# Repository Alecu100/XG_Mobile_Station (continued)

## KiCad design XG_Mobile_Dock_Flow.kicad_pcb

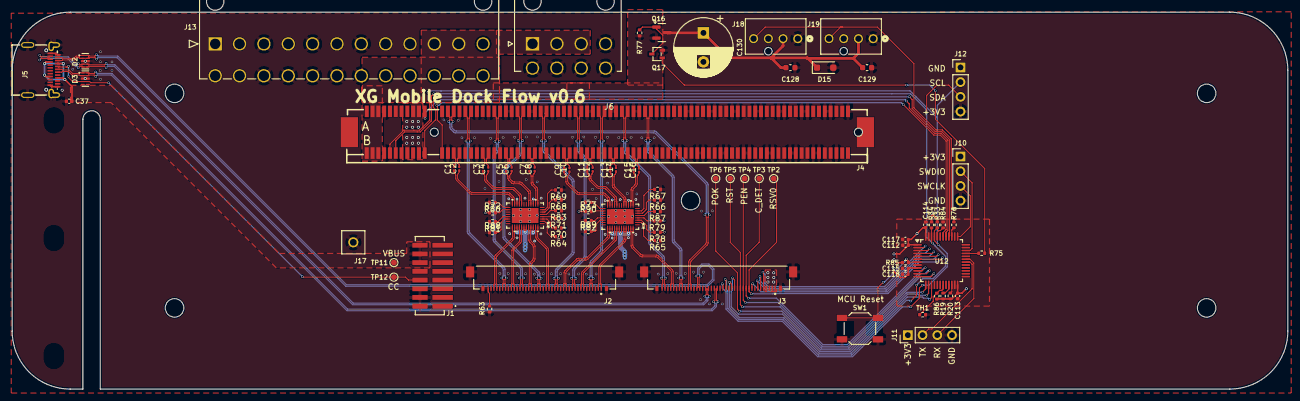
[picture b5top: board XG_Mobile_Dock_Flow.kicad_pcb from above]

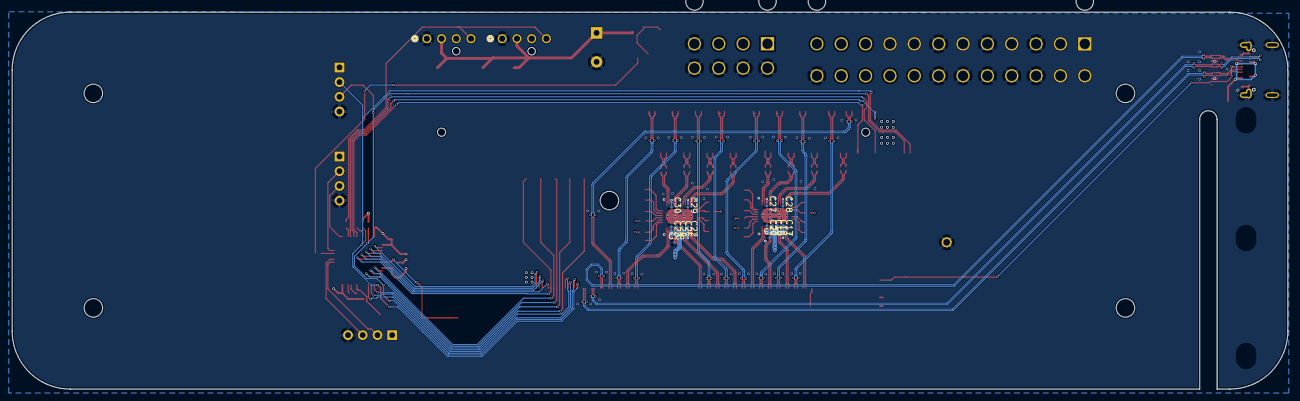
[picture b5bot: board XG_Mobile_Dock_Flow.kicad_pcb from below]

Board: 4 copper layers, 220.0 x 65.0 mm, 101 parts (14 on the bottom side), 133 nets.

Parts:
C1, C2, C3, C4, C5, C6, C7, C8, C9, C10, C11, C12, C13, C14, C15, C16: 220nF; C_0201_0603Metric
C17, C18, C19, C20, C22, C23, C24, C25, C27, C28, C29, C30: 100nF; C_0201_0603Metric
C21, C26: 1μF; C_0201_0603Metric
C37: 0.1μF; C_0402_1005Metric
C112, C113, C114: 0.1µF; C_0402_1005Metric
C115: 10nF; C_0402_1005Metric
C117: 4.7µF; C_0402_1005Metric
C118: 1µF; C_0402_1005Metric
C128, C129: 0.1µF; C_0603_1608Metric
C130: 470µF; CP_Radial_D10.0mm_P5.00mm
D2, D3: H5VU25U; AZ1045-04F
D15: 1N4007; D_SOD-123F
J1: 5-1775443-8
J2, J3: 20455-040E-76
J4: 3-2362375-4; CONN-SMD_164P-P1.00-V_3133
J5: USB_C_Receptacle; USB-C-SMD_TYPE-C-24P-QT
J6: 455860005; MOLEX_455860005
J10: SWD; PinHeader_1x04_P2.54mm_Vertical
J11: UART; PinHeader_1x04_P2.54mm_Vertical
J12: I2C1; PinHeader_1x04_P2.54mm_Vertical
J13: 39301240; CON_39300240
J17: 8730; KEYSTONE_8730
J18, J19: CONN_SD-47053-001_H10p00_MOL
Q16: AO3401A; SOT-23
Q17: 2N7002W; SOT-323-3_L2.0-W1.3-P1.30-LS2.1-BR
R19, R20, R70, R71, R72, R73, R78, R79, R80, R81, R82, R90: 4.7k; R_0402_1005Metric
R33, R34, R63, R77, R85: 10k; R_0402_1005Metric
R64, R65, R84, R88, R89: 1k; R_0402_1005Metric
R66, R67, R68, R69, R83, R87: 59k; R_0402_1005Metric
R75: 100; R_0402_1005Metric
R76: 330; R_0402_1005Metric
R86: 100k; R_0402_1005Metric
SW1: SW_Push; SW_SPST_SKQG_WithStem
TH1: NCP15WF104F03RC; R_0402_1005Metric
TP2, TP3, TP4, TP5, TP6, TP11, TP12: TestPoint_Small; TestPoint_Pad_D1.0mm
U1, U2: DS160PR410RNQR; WQFN_RNQ40_TEX
U12: STM32F030C8Tx; LQFP-48_7x7mm_P0.5mm

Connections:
+3V3: C17.2, C18.2, C19.2, C20.2, C21.2, C22.2, C23.2, C24.2, C25.2, C26.2, C112.1, C113.1, C114.1, C115.1, C117.1, C118.1, J3.1 (+3.3V), J3.2 (+3.3V), J3.3 (+3.3V), J3.4 (+3.3V), J4.A9, J4.A10, J4.B8, J4.B10, J10.1, J11.1, J12.1, J13.1, J13.2, J13.12, J13.13, R19.1, R20.1, R33.1, R34.1, R70.1, R71.1, R72.1, R73.1, R78.1, R79.1, R85.2, R86.2, U1.31 (VDD), U1.34 (VDD), U1.35 (VDD), U1.38 (VDD), U2.31 (VDD), U2.34 (VDD), U2.35 (VDD), U2.38 (VDD), U12.1 (VDD), U12.9 (VDDA), U12.24 (VDD), U12.48 (VDD)
+12V: J4.A2, J4.A3, J4.B1, J4.B2, J4.B3, J6.1, J6.2, J6.3, J13.10, J13.11, Q16.2 (S), R77.1
/AC_LOSS: J3.15 (P_AC_LOSS), U12.14 (PA4)
/CC: D3.4 (I/O_3), D3.7 (NC), J1.13 (CC), J5.A5 (CC1), TP12.1
/CLKN: J3.30 (PCIE_CLKN), J4.A14
/CLKP: J3.31 (PCIE_CLKP), J4.A13
/CLKREQ#: J4.B12, U12.42 (PB6)
/CON_DET: J3.11 (CON_DET), TP3.1, U12.10 (PA0)
/C_DN: D3.2 (I/O_2), D3.9 (NC), J3.21 (USB_DM), J5.A7 (D-)
/C_DP: D3.1 (I/O_1), D3.10 (NC), J3.22 (USB_DP), J5.A6 (D+)
/C_RXN: D2.5 (I/O_4), D2.6 (NC), J3.24 (USB_RXN), J5.B10 (RX1-)
/C_RXP: D2.4 (I/O_3), D2.7 (NC), J3.25 (USB_RXP), J5.B11 (RX1+)
/C_TXN: D2.2 (I/O_2), D2.9 (NC), J3.28 (USB_TXP), J5.A3 (TX1-)
/C_TXP: D2.1 (I/O_1), D2.10 (NC), J3.27 (USB_TXN), J5.A2 (TX1+)
/DET: J2.40 (CON_DET_TOWER#), R63.1
/HSI0N: J2.34 (PCIE_RXN0), J4.A17
/HSI0P: J2.35 (PCIE_RXP0), J4.A16
/HSI1N: J2.28 (PCIE_RXN1), J4.A22
/HSI1P: J2.29 (PCIE_RXP1), J4.A21
/HSI2N: J2.22 (PCIE_RXN2), J4.A26
/HSI2P: J2.23 (PCIE_RXP2), J4.A25
/HSI3N: J2.16 (PCIE_RXN3), J4.A30
/HSI3P: J2.17 (PCIE_RXP3), J4.A29
/HSI4N: J2.10 (PCIE_RXN4), J4.A36
/HSI4P: J2.11 (PCIE_RXP4), J4.A35
/HSI5N: J2.4 (PCIE_RXN5), J4.A40
/HSI5P: J2.5 (PCIE_RXP5), J4.A39
/HSI6N: J3.39 (PCIE_RXN6), J4.A44
/HSI6P: J3.40 (PCIE_RXP6), J4.A43
/HSI7N: J3.33 (PCIE_RXN7), J4.A48
/HSI7P: J3.34 (PCIE_RXP7), J4.A47
/HSO0N: C2.2, J4.B15
/HSO0P: C1.2, J4.B14
/HSO1N: C4.2, J4.B20
/HSO1P: C3.2, J4.B19
/HSO2N: C6.2, J4.B24
/HSO2P: C5.2, J4.B23
/HSO3N: C8.2, J4.B28
/HSO3P: C7.2, J4.B27
/HSO4N: C10.2, J4.B34
/HSO4P: C9.2, J4.B33
/HSO5N: C12.2, J4.B38
/HSO5P: C11.2, J4.B37
/HSO6N: C14.2, J4.B42
/HSO6P: C13.2, J4.B41
/HSO7N: C16.2, J4.B46
/HSO7P: C15.2, J4.B45
/HSOL0N: J2.37 (PCIE_TXN0), U1.30 (RX0N)
/HSOL0P: J2.38 (PCIE_TXP0), U1.29 (RX0P)
/HSOL1N: J2.31 (PCIE_TXN1), U1.33 (RX1N)
/HSOL1P: J2.32 (PCIE_TXP1), U1.32 (RX1P)
/HSOL2N: J2.25 (PCIE_TXN2), U1.37 (RX2N)
/HSOL2P: J2.26 (PCIE_TXP2), U1.36 (RX2P)
/HSOL3N: J2.19 (PCIE_TXN3), U1.40 (RX3N)
/HSOL3P: J2.20 (PCIE_TXP3), U1.39 (RX3P)
/HSOL4N: J2.13 (PCIE_TXN4), U2.30 (RX0N)
/HSOL4P: J2.14 (PCIE_TXP4), U2.29 (RX0P)
/HSOL5N: J2.7 (PCIE_TXN5), U2.33 (RX1N)
/HSOL5P: J2.8 (PCIE_TXP5), U2.32 (RX1P)
/HSOL6N: J2.1 (PCIE_TXN6), U2.37 (RX2N)
/HSOL6P: J2.2 (PCIE_TXP6), U2.36 (RX2P)
/HSOL7N: J3.36 (PCIE_TXN7), U2.40 (RX3N)
/HSOL7P: J3.37 (PCIE_TXP7), U2.39 (RX3P)
/HSOT0N: C2.1, U1.19 (TX0N)
/HSOT0P: C1.1, U1.20 (TX0P)
/HSOT1N: C4.1, U1.16 (TX1N)
/HSOT1P: C3.1, U1.17 (TX1P)
/HSOT2N: C6.1, U1.12 (TX2N)
/HSOT2P: C5.1, U1.13 (TX2P)
/HSOT3N: C8.1, U1.9 (TX3N)
/HSOT3P: C7.1, U1.10 (TX3P)
/HSOT4N: C10.1, U2.19 (TX0N)
/HSOT4P: C9.1, U2.20 (TX0P)
/HSOT5N: C12.1, U2.16 (TX1N)
/HSOT5P: C11.1, U2.17 (TX1P)
/HSOT6N: C14.1, U2.12 (TX2N)
/HSOT6P: C13.1, U2.13 (TX2P)
/HSOT7N: C16.1, U2.9 (TX3N)
/HSOT7P: C15.1, U2.10 (TX3P)
/LED_RED#: J3.7 (LED_R), U12.4 (PC15)
/LED_WHITE#: J3.6 (LED_W), U12.3 (PC14)
/LOCK_DET: J3.9 (CON_SW1_DET), U12.5 (PF0)
/LOCK_SW: J3.5 (LOCK_SW), U12.2 (PC13)
/MCU/FAN_ON: R75.1, U12.33 (PA12)
/MCU/FAN_PWM: R76.1, U12.39 (PB3)
/MCU/RX: J11.3, U12.31 (PA10)
/MCU/SCL2: R19.2, U12.21 (PB10)
/MCU/SDA2: R20.2, U12.22 (PB11)
/MCU/SWCLK: J10.3, U12.37 (PA14)
/MCU/SWDIO: J10.2, U12.34 (PA13)
/MCU/TX: J11.2, U12.30 (PA9)
/MCU_IRQ#: J3.16 (MCU_IRQ#), U12.15 (PA5)
/PERST#: J4.A11, U12.41 (PB5)
/PWREN#: J3.12 (PWR_EN#), TP4.1, U12.11 (PA1)
/PWROK: J3.14 (PWROK), TP6.1, U12.13 (PA3)
/RST#: J3.13 (RST#), TP5.1, U12.12 (PA2)
/RST_SW: R85.1, SW1.1, U12.7 (NRST)
/RSV0: J3.10, TP2.1, U12.6 (PF1)
/SCL: J3.19 (SMB1_CLK), J4.B5, J12.2, R33.2, U12.45 (PB8)
/SDA: J3.18 (SMB1_DAT), J4.B6, J12.3, R34.2, U12.46 (PB9)
/VBUS: C37.1, J1.9 (VBUS), J1.10 (VBUS), J1.11 (VBUS), J5.A4 (VBUS), J5.A9 (VBUS), J5.B4 (VBUS), J5.B9 (VBUS), TP11.1
/WAKE#: J4.B11, U12.40 (PB4)
GND: C17.1, C18.1, C19.1, C20.1, C21.1, C22.1, C23.1, C24.1, C25.1, C26.1, C27.2, C28.2, C29.2, C30.2, C37.2, C112.2, C113.2, C114.2, C115.2, C117.2, C118.2, C128.2, C129.2, C130.2, D2.3 (GND), D2.8 (GND), D3.3 (GND), D3.8 (GND), D15.2 (A), J1.14 (GND), J1.15 (GND), J1.16 (GND), J2.3 (GND), J2.6 (GND), J2.9 (GND), J2.12 (GND), J2.15 (GND), J2.18 (GND), J2.21 (GND), J2.24 (GND), J2.27 (GND), J2.30 (GND), J2.33 (GND), J2.36 (GND), J2.39 (GND), J2.S1 (SHIELD), J2.S2 (SHIELD), J2.S3 (SHIELD), J2.S4 (SHIELD), J3.17 (GND), J3.20 (GND), J3.23 (GND), J3.26 (GND), J3.29 (GND), J3.32 (GND), J3.35 (GND), J3.38 (GND), J3.S1 (SHIELD), J3.S2 (SHIELD), J3.S3 (SHIELD), J3.S4 (SHIELD), J4.A4, J4.A12, J4.A15, J4.A18, J4.A20, J4.A23, J4.A24, J4.A27, J4.A28, J4.A31, J4.A34, J4.A37, J4.A38, J4.A41, J4.A42, J4.A45, J4.A46, J4.A49, J4.A51, J4.A54, J4.A55, J4.A58, J4.A59, J4.A62, J4.A63, J4.A66, J4.A67, J4.A70, J4.A71, J4.A74, J4.A75, J4.A78, J4.A79, J4.A82, J4.B4, J4.B7, J4.B13, J4.B16, J4.B18, J4.B21, J4.B22, J4.B25, J4.B26, J4.B29, J4.B32, J4.B35, J4.B36, J4.B39, J4.B40, J4.B43, J4.B44, J4.B47, J4.B49, J4.B52, J4.B53, J4.B56, J4.B57, J4.B60, J4.B61, J4.B64, J4.B65, J4.B68, J4.B69, J4.B72, J4.B73, J4.B76, J4.B77, J4.B80, J5.A1 (GND), J5.A12 (GND), J5.B1 (GND), J5.B12 (GND), J5.S1 (SHIELD), J6.4, J6.5, J6.6, J6.7, J6.8, J10.4, J11.4, J12.4, J13.3, J13.5, J13.7, J13.15, J13.16, J13.17, J13.18, J13.19, J13.24, J17.1, J18.1, J19.1, Q17.2 (S), R63.2, R64.1, R65.1, R66.1, R67.1, R68.1, R69.1, R80.2, R81.2, R82.2, R83.1, R84.1, R87.1, R88.1, R89.1, R90.2, SW1.2, TH1.2, U1.41 (GND), U2.41 (GND), U12.8 (VSSA), U12.23 (VSS), U12.47 (VSS)
unnamed: C128.1, C129.1, C130.1, D15.1 (K), J18.2, J19.2, Q16.3 (D)
unnamed: J18.4, J19.4, R76.2
unnamed: Q16.1 (G), Q17.3 (D), R77.2
unnamed: Q17.1 (G), R75.2
unnamed: R64.2, U1.2 (EN_SMB)
unnamed: R69.2, U1.7 (EQ0_ADDR0)
unnamed: R68.2, U1.6 (EQ1_ADDR1)
unnamed: R83.2, U1.5 (GAIN)
unnamed: R80.1, U1.21 (PWDN1)
unnamed: R81.1, U1.25 (PWDN2)
unnamed: R72.2, U1.22 (READ_EN_N)
unnamed: R88.2, U1.26 (RX_DET)
unnamed: R70.2, U1.3 (SCL)
unnamed: R71.2, U1.4 (SDA)
unnamed: C28.1, U1.18 (VREF)
unnamed: C27.1, U1.11 (VREG)
unnamed: R65.2, U2.2 (EN_SMB)
unnamed: R67.2, U2.7 (EQ0_ADDR0)
unnamed: R66.2, U2.6 (EQ1_ADDR1)
unnamed: R87.2, U2.5 (GAIN)
unnamed: R90.1, U2.21 (PWDN1)
unnamed: R82.1, U2.25 (PWDN2)
unnamed: R73.2, U2.22 (READ_EN_N)
unnamed: R89.2, U2.26 (RX_DET)
unnamed: R78.2, U2.3 (SCL)
unnamed: R79.2, U2.4 (SDA)
unnamed: C29.1, U2.18 (VREF)
unnamed: C30.1, U2.11 (VREG)
unnamed: R84.2, U12.44 (BOOT0)
unnamed: R86.1, TH1.1, U12.19 (PB1)

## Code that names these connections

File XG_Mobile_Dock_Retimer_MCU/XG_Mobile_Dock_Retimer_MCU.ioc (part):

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Mcu.Name=STM32F405RGTx
Mcu.Package=LQFP64
Mcu.UserName=STM32F405RGTx
PA0-WKUP.GPIOParameters=GPIO_PuPd,GPIO_Label,GPIO_ModeDefaultEXTI
PA0-WKUP.GPIO_Label=CON_DET
PA0-WKUP.GPIO_ModeDefaultEXTI=GPIO_MODE_IT_RISING_FALLING
PA0-WKUP.GPIO_PuPd=GPIO_PULLUP
PA0-WKUP.Signal=GPXTI0
PA1.GPIOParameters=GPIO_PuPd,GPIO_Label,GPIO_ModeDefaultEXTI
PA1.GPIO_Label=PWREN
PA1.GPIO_ModeDefaultEXTI=GPIO_MODE_IT_RISING_FALLING
PA1.GPIO_PuPd=GPIO_PULLUP
PA1.Signal=GPXTI1
PA2.GPIOParameters=GPIO_PuPd,GPIO_Label,GPIO_ModeDefaultEXTI
PA2.GPIO_Label=RST
PA2.GPIO_ModeDefaultEXTI=GPIO_MODE_IT_RISING_FALLING
PA2.GPIO_PuPd=GPIO_PULLUP
PA2.Signal=GPXTI2
PA3.GPIOParameters=PinState,GPIO_Label
PA3.GPIO_Label=PWROK
PA3.PinState=GPIO_PIN_RESET
PA3.Signal=GPIO_Output
PA4.GPIOParameters=PinState,GPIO_PuPd,GPIO_Label
PA4.GPIO_Label=AC_LOSS
PA4.GPIO_PuPd=GPIO_PULLDOWN
PA4.PinState=GPIO_PIN_RESET
PA4.Signal=GPIO_Output
PA5.GPIOParameters=PinState,GPIO_PuPd,GPIO_Label,GPIO_ModeDefaultOutputPP
PA5.GPIO_Label=MCU_IRQ
PA5.GPIO_ModeDefaultOutputPP=GPIO_MODE_OUTPUT_OD
PA5.GPIO_PuPd=GPIO_PULLUP
PA5.PinState=GPIO_PIN_SET
PA5.Signal=GPIO_Output
PA6.GPIOParameters=PinState,GPIO_PuPd,GPIO_Label,GPIO_ModeDefaultOutputPP
PA6.GPIO_Label=PCI_12V_EN
PA6.GPIO_ModeDefaultOutputPP=GPIO_MODE_OUTPUT_OD
PA6.GPIO_PuPd=GPIO_NOPULL
PA6.PinState=GPIO_PIN_RESET
PA6.Signal=GPIO_Output
PA8.GPIOParameters=PinState,GPIO_Label
PA8.GPIO_Label=FAN_ON
PA8.PinState=GPIO_PIN_RESET
PA8.Signal=GPIO_Output
PA9.Mode=Device_Only
PA9.Signal=USB_OTG_FS_VBUS
PA11.Mode=Device_Only
PA11.Signal=USB_OTG_FS_DM
PA12.Mode=Device_Only
PA12.Signal=USB_OTG_FS_DP
PA13.Mode=Serial_Wire
PA13.Signal=SYS_JTMS-SWDIO
PA14.Mode=Serial_Wire
PA14.Signal=SYS_JTCK-SWCLK
PB1.Mode=IN9
PB1.Signal=ADC1_IN9
PB2.GPIOParameters=PinState,GPIO_Label
PB2.GPIO_Label=PSON
PB2.PinState=GPIO_PIN_RESET
PB2.Signal=GPIO_Output
PB3.GPIOParameters=GPIO_Speed,PinState,GPIO_Label
PB3.GPIO_Label=FAN_PWM
PB3.GPIO_Speed=GPIO_SPEED_FREQ_HIGH
PB3.PinState=GPIO_PIN_RESET
PB3.Signal=GPIO_Output
PB4.GPIOParameters=PinState,GPIO_PuPd,GPIO_Label,GPIO_ModeDefaultOutputPP
PB4.GPIO_Label=WAKE
PB4.GPIO_ModeDefaultOutputPP=GPIO_MODE_OUTPUT_OD
PB4.GPIO_PuPd=GPIO_PULLUP
PB4.PinState=GPIO_PIN_SET
PB4.Signal=GPIO_Output
PB5.GPIOParameters=PinState,GPIO_Label
PB5.GPIO_Label=PERST
PB5.PinState=GPIO_PIN_SET
PB5.Signal=GPIO_Output
PB6.GPIOParameters=PinState,GPIO_Label,GPIO_ModeDefaultOutputPP
PB6.GPIO_Label=CLKREQ
PB6.GPIO_ModeDefaultOutputPP=GPIO_MODE_OUTPUT_OD
PB6.PinState=GPIO_PIN_RESET
PB6.Signal=GPIO_Output
PB8.Mode=I2C
PB8.Signal=I2C1_SCL
PB9.Mode=I2C
PB9.Signal=I2C1_SDA
PB10.Mode=I2C
PB10.Signal=I2C2_SCL
PB11.Mode=I2C
PB11.Signal=I2C2_SDA
PB12.GPIOParameters=GPIO_Label
PB12.GPIO_Label=PGOOD_BUCK
PB12.Signal=GPIO_Input
PC0.GPIOParameters=PinState,GPIO_Label
PC0.GPIO_Label=RETIMER_PERST
PC0.PinState=GPIO_PIN_SET
PC0.Signal=GPIO_Output
PC1.GPIOParameters=PinState,GPIO_PuPd,GPIO_Label,GPIO_ModeDefaultOutputPP
PC1.GPIO_Label=RETIMER_CLKREQ
PC1.GPIO_ModeDefaultOutputPP=GPIO_MODE_OUTPUT_OD
PC1.GPIO_PuPd=GPIO_PULLUP
PC1.PinState=GPIO_PIN_RESET
PC1.Signal=GPIO_Output
PC3.GPIOParameters=PinState,GPIO_Label
PC3.GPIO_Label=BUCK_ON
PC3.PinState=GPIO_PIN_RESET
PC3.Signal=GPIO_Output
PC4.GPIOParameters=GPIO_PuPd,GPIO_Label,GPIO_ModeDefaultEXTI
PC4.GPIO_Label=LOCK_SW
PC4.GPIO_ModeDefaultEXTI=GPIO_MODE_IT_RISING_FALLING
PC4.GPIO_PuPd=GPIO_PULLUP
PC4.Signal=GPXTI4
PC8.GPIOParameters=PinState,GPIO_PuPd,GPIO_Label,GPIO_ModeDefaultOutputPP
PC8.GPIO_Label=CASE_LED
PC8.GPIO_ModeDefaultOutputPP=GPIO_MODE_OUTPUT_OD
PC8.GPIO_PuPd=GPIO_NOPULL
PC8.PinState=GPIO_PIN_SET
PC8.Signal=GPIO_Output
PC9.GPIOParameters=PinState,GPIO_PuPd,GPIO_Label,GPIO_ModeDefaultOutputPP
PC9.GPIO_Label=LED_WHITE
PC9.GPIO_ModeDefaultOutputPP=GPIO_MODE_OUTPUT_OD
PC9.GPIO_PuPd=GPIO_NOPULL
PC9.PinState=GPIO_PIN_SET
PC9.Signal=GPIO_Output
PC10.Mode=Asynchronous
PC10.Signal=USART3_TX
PC11.Mode=Asynchronous
PC11.Signal=USART3_RX
PD2.GPIOParameters=PinState,GPIO_PuPd,GPIO_Label,GPIO_ModeDefaultOutputPP
PD2.GPIO_Label=LED_RED
PD2.GPIO_ModeDefaultOutputPP=GPIO_MODE_OUTPUT_OD
PD2.GPIO_PuPd=GPIO_NOPULL
PD2.PinState=GPIO_PIN_SET
PD2.Signal=GPIO_Output
PC6.GPIOParameters=PinState,GPIO_Label
PC6.GPIO_Label=LOCK_DET
PC6.PinState=GPIO_PIN_RESET
PC6.Signal=GPIO_Output
PC7.GPIOParameters=GPIO_Label
PC7.GPIO_Label=RSV0
PC7.Signal=GPIO_Input
PH0-OSC_IN.Mode=HSE-External-Oscillator
PH0-OSC_IN.Signal=RCC_OSC_IN
PH1-OSC_OUT.Mode=HSE-External-Oscillator
PH1-OSC_OUT.Signal=RCC_OSC_OUT
RCC.HSE_VALUE=8000000
RCC.SYSCLKFreq_VALUE=168000000
RCC.SYSCLKSource=RCC_SYSCLKSOURCE_PLLCLK
board=custom

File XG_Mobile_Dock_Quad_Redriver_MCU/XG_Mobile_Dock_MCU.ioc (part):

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Mcu.Name=STM32F030C8Tx
Mcu.Package=LQFP48
Mcu.UserName=STM32F030C8Tx
PA0.GPIOParameters=GPIO_PuPd,GPIO_Label,GPIO_ModeDefaultEXTI
PA0.GPIO_Label=CON_DET
PA0.GPIO_ModeDefaultEXTI=GPIO_MODE_IT_RISING_FALLING
PA0.GPIO_PuPd=GPIO_PULLUP
PA0.Signal=GPXTI0
PA1.GPIOParameters=GPIO_PuPd,GPIO_Label,GPIO_ModeDefaultEXTI
PA1.GPIO_Label=PWREN
PA1.GPIO_ModeDefaultEXTI=GPIO_MODE_IT_RISING_FALLING
PA1.GPIO_PuPd=GPIO_PULLUP
PA1.Signal=GPXTI1
PA10.Mode=Asynchronous
PA10.Signal=USART1_RX
PA12.GPIOParameters=PinState,GPIO_Label
PA12.GPIO_Label=FAN_ON
PA12.PinState=GPIO_PIN_RESET
PA12.Signal=GPIO_Output
PA13.Mode=Serial_Wire
PA13.Signal=SYS_SWDIO
PA14.Mode=Serial_Wire
PA14.Signal=SYS_SWCLK
PA15.GPIOParameters=PinState,GPIO_PuPd,GPIO_Label,GPIO_ModeDefaultOutputPP
PA15.GPIO_Label=PCI_12V_EN
PA15.GPIO_ModeDefaultOutputPP=GPIO_MODE_OUTPUT_OD
PA15.GPIO_PuPd=GPIO_NOPULL
PA15.PinState=GPIO_PIN_RESET
PA15.Signal=GPIO_Output
PA2.GPIOParameters=GPIO_PuPd,GPIO_Label,GPIO_ModeDefaultEXTI
PA2.GPIO_Label=RST
PA2.GPIO_ModeDefaultEXTI=GPIO_MODE_IT_RISING_FALLING
PA2.GPIO_PuPd=GPIO_PULLUP
PA2.Signal=GPXTI2
PA3.GPIOParameters=PinState,GPIO_PuPd,GPIO_Label,GPIO_ModeDefaultOutputPP
PA3.GPIO_Label=PWROK
PA3.GPIO_ModeDefaultOutputPP=GPIO_MODE_OUTPUT_PP
PA3.GPIO_PuPd=GPIO_NOPULL
PA3.PinState=GPIO_PIN_RESET
PA3.Signal=GPIO_Output
PA4.GPIOParameters=PinState,GPIO_PuPd,GPIO_Label,GPIO_ModeDefaultOutputPP
PA4.GPIO_Label=AC_LOSS
PA4.GPIO_ModeDefaultOutputPP=GPIO_MODE_OUTPUT_PP
PA4.GPIO_PuPd=GPIO_PULLDOWN
PA4.PinState=GPIO_PIN_RESET
PA4.Signal=GPIO_Output
PA5.GPIOParameters=PinState,GPIO_PuPd,GPIO_Label,GPIO_ModeDefaultOutputPP
PA5.GPIO_Label=MCU_IRQ
PA5.GPIO_ModeDefaultOutputPP=GPIO_MODE_OUTPUT_OD
PA5.GPIO_PuPd=GPIO_PULLUP
PA5.PinState=GPIO_PIN_SET
PA5.Signal=GPIO_Output
PA9.Mode=Asynchronous
PA9.Signal=USART1_TX
PB1.Mode=IN9
PB1.Signal=ADC_IN9
PB10.GPIOParameters=GPIO_Pu
PB10.GPIO_Pu=GPIO_NOPULL
PB10.Mode=I2C
PB10.Signal=I2C2_SCL
PB11.GPIOParameters=GPIO_Speed,GPIO_Pu
PB11.GPIO_Pu=GPIO_NOPULL
PB11.GPIO_Speed=GPIO_SPEED_FREQ_HIGH
PB11.Mode=I2C
PB11.Signal=I2C2_SDA
PB12.GPIOParameters=GPIO_PuPd,GPIO_Label,GPIO_ModeDefaultOutputPP
PB12.GPIO_Label=CPU_GPU_PD_0-3
PB12.GPIO_ModeDefaultOutputPP=GPIO_MODE_OUTPUT_OD
PB12.GPIO_PuPd=GPIO_PULLUP
PB12.Signal=GPIO_Output
PB13.GPIOParameters=GPIO_PuPd,GPIO_Label,GPIO_ModeDefaultOutputPP
PB13.GPIO_Label=CPU_GPU_PD_4-7
PB13.GPIO_ModeDefaultOutputPP=GPIO_MODE_OUTPUT_OD
PB13.GPIO_PuPd=GPIO_PULLUP
PB13.Signal=GPIO_Output
PB14.GPIOParameters=GPIO_PuPd,GPIO_Label,GPIO_ModeDefaultOutputPP
PB14.GPIO_Label=GPU_CPU_PD-0-3
PB14.GPIO_ModeDefaultOutputPP=GPIO_MODE_OUTPUT_OD
PB14.GPIO_PuPd=GPIO_PULLUP
PB14.Signal=GPIO_Output
PB15.GPIOParameters=GPIO_PuPd,GPIO_Label,GPIO_ModeDefaultOutputPP
PB15.GPIO_Label=GPU_CPU_PD-4-7
PB15.GPIO_ModeDefaultOutputPP=GPIO_MODE_OUTPUT_OD
PB15.GPIO_PuPd=GPIO_PULLUP
PB15.Signal=GPIO_Output
PB2.GPIOParameters=PinState,GPIO_Label
PB2.GPIO_Label=PSON
PB2.PinState=GPIO_PIN_RESET
PB2.Signal=GPIO_Output
PB3.GPIOParameters=GPIO_Speed,PinState,GPIO_Label
PB3.GPIO_Label=FAN_PWM
PB3.GPIO_Speed=GPIO_SPEED_FREQ_HIGH
PB3.PinState=GPIO_PIN_RESET
PB3.Signal=GPIO_Output
PB4.GPIOParameters=PinState,GPIO_PuPd,GPIO_Label,GPIO_ModeDefaultOutputPP
PB4.GPIO_Label=WAKE
PB4.GPIO_ModeDefaultOutputPP=GPIO_MODE_OUTPUT_OD
PB4.GPIO_PuPd=GPIO_PULLUP
PB4.PinState=GPIO_PIN_SET
PB4.Signal=GPIO_Output
PB5.GPIOParameters=PinState,GPIO_PuPd,GPIO_Label,GPIO_ModeDefaultOutputPP
PB5.GPIO_Label=PERST
PB5.GPIO_ModeDefaultOutputPP=GPIO_MODE_OUTPUT_PP
PB5.GPIO_PuPd=GPIO_NOPULL
PB5.PinState=GPIO_PIN_SET
PB5.Signal=GPIO_Output
PB6.GPIOParameters=PinState,GPIO_PuPd,GPIO_Label,GPIO_ModeDefaultOutputPP
PB6.GPIO_Label=CLKREQ
PB6.GPIO_ModeDefaultOutputPP=GPIO_MODE_OUTPUT_OD
PB6.GPIO_PuPd=GPIO_PULLUP
PB6.PinState=GPIO_PIN_SET
PB6.Signal=GPIO_Output
PB8.Mode=I2C
PB8.Signal=I2C1_SCL
PB9.Mode=I2C
PB9.Signal=I2C1_SDA
PC13.GPIOParameters=GPIO_PuPd,GPIO_Label,GPIO_ModeDefaultEXTI
PC13.GPIO_Label=LOCK_SW
PC13.GPIO_ModeDefaultEXTI=GPIO_MODE_IT_RISING_FALLING
PC13.GPIO_PuPd=GPIO_PULLUP
PC13.Signal=GPXTI13
PC14-OSC32_IN.GPIOParameters=PinState,GPIO_PuPd,GPIO_Label,GPIO_ModeDefaultOutputPP
PC14-OSC32_IN.GPIO_Label=LED_WHITE
PC14-OSC32_IN.GPIO_ModeDefaultOutputPP=GPIO_MODE_OUTPUT_OD
PC14-OSC32_IN.GPIO_PuPd=GPIO_NOPULL
PC14-OSC32_IN.PinState=GPIO_PIN_SET
PC14-OSC32_IN.Signal=GPIO_Output
PC15-OSC32_OUT.GPIOParameters=PinState,GPIO_PuPd,GPIO_Label,GPIO_ModeDefaultOutputPP
PC15-OSC32_OUT.GPIO_Label=LED_RED
PC15-OSC32_OUT.GPIO_ModeDefaultOutputPP=GPIO_MODE_OUTPUT_OD
PC15-OSC32_OUT.GPIO_PuPd=GPIO_NOPULL
PC15-OSC32_OUT.PinState=GPIO_PIN_SET
PC15-OSC32_OUT.Signal=GPIO_Output
PF0-OSC_IN.GPIOParameters=GPIO_Label
PF0-OSC_IN.GPIO_Label=LOCK_DET
PF0-OSC_IN.Signal=GPIO_Output
PF1-OSC_OUT.GPIOParameters=GPIO_Label
PF1-OSC_OUT.GPIO_Label=RSV0
PF1-OSC_OUT.Signal=GPIO_Input
PF7.GPIOParameters=PinState,GPIO_PuPd,GPIO_Label,GPIO_ModeDefaultOutputPP
PF7.GPIO_Label=CASE_LED
PF7.GPIO_ModeDefaultOutputPP=GPIO_MODE_OUTPUT_OD
PF7.GPIO_PuPd=GPIO_NOPULL
PF7.PinState=GPIO_PIN_SET
PF7.Signal=GPIO_Output
RCC.SYSCLKFreq_VALUE=32000000
RCC.SYSCLKSource=RCC_SYSCLKSOURCE_PLLCLK
board=custom

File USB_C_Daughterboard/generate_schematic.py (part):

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    hub_nets[str(index)] = net
part(hub,'U501','USB7206CT_KDX',hub_nets,mpn='USB7206CT/KDX',lcsc='C3210691')
define('Crystal', [('1','XI','passive'),('3','XO','passive'),('2','GND','passive'),('4','GND','passive')])
part(hub,'Y501','Crystal',{'1':'HUB_XTALI','3':'HUB_XTALO','2':'GND','4':'GND'},'25MHz CL=18pF',mpn='ABM8-25.000MHZ-B2-T',footprint='Crystal:Crystal_SMD_3225-4Pin_3.2x2.5mm')
passive(hub,'C501','27pF C0G - tune CL','HUB_XTALI','GND')
passive(hub,'C502','27pF C0G - tune CL','HUB_XTALO','GND')
passive(hub,'R501','12k 1%','HUB_RBIAS','GND')
straps = [('CFG_STRAP1','10k','GND'),('CFG_STRAP2','200k','GND'),('CFG_STRAP3','200k','GND'),('SPI_CE_N','200k','GND'),('SPI_D0','200k','GND'),('TEST1','10k','V3V3'),('TEST2','10k','V3V3'),('TEST3','10k','V3V3')]
for index,(name,value,rail) in enumerate(straps,502):
    passive(hub,f'R{index}',value,'HUB_'+name,rail)
for index,name in enumerate(['PF3','PF4','PF5','PF6','PF7','PF18','PF19','PF31','SPI_CLK','SPI_D1','SPI_D2','SPI_D3','PF29'],510):
    passive(hub,f'R{index}','100k','HUB_'+name,'GND')
hub_nets['75'] = 'I2C_SCL'
hub_nets['76'] = 'I2C_SDA'
passive(hub,'R523','100k','HUB_RESET_N','GND')
passive(hub,'R524','100k','HUB_VBUS_DET','GND')
decoupling = sheet('Hub_Decoupling', 'Hub decoupling and transmit coupling', 'One 100 nF capacitor per VDD33/VCORE pin, placed at the relevant pin. Bulk capacitors near hub.\n220 nF series capacitors on each hub SuperSpeed TX lane only. Route 90 ohm differential pairs without stubs.')
for index in range(503,512):
    passive(decoupling,f'C{index}','100nF','VCORE','GND')
for index in range(512,521):
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    'power_in' if name in ['VBAT','VREF+','VDD/VDDA','VSS/VSSA'] else
    'input' if name=='PF2-NRST' else 'bidirectional')
    for index,name in enumerate([
        'PC13','PC14-OSC32_IN','PC15-OSC32_OUT','VBAT','VREF+','VDD/VDDA','VSS/VSSA',
        'PF0-OSC_IN','PF1-OSC_OUT','PF2-NRST','PA0','PA1','PA2','PA3','PA4','PA5','PA6','PA7',
        'PB0','PB1','PB2','PB10','PB11','PB12','PB13','PB14','PB15','PA8','PA9/UCPD1_DBCC1',
        'PC6','PC7','PA10/UCPD1_DBCC2','PA11[PA9]','PA12[PA10]','PA13','PA14-BOOT0','PA15',
        'PD0','PD1/UCPD2_DBCC1','PD2','PD3/UCPD2_DBCC2','PB3','PB4','PB5','PB6','PB7','PB8','PB9'],1)],
    'Package_QFP:LQFP-48_7x7mm_P0.5mm','https://www.st.com/resource/en/datasheet/stm32g071cb.pdf')
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part(mcu,'U1300','STM32G071CBT6',dict(zip(map(str,range(1,49)),[
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    'P1_ID_N','P2_ID_N','SWDIO','SWCLK',None,'UP_FAULT_N','PD_NFLT','UP_MUX_SEL','UP_MUX_OEN',
    None,None,None,'I2C_SCL','I2C_SDA','CORE_PG','3V3_PG'])),lcsc='C432212')
define('SWD_5',[(str(index),name,'passive') for index,name in enumerate(['VTREF','SWDIO','SWCLK','NRST','GND'],1)])
part(mcu,'J1300','SWD_5',{'1':'V3V3','2':'SWDIO','3':'SWCLK','4':'MCU_NRST','5':'GND'},mpn='SWD 1x5 2.54mm',footprint='Connector_PinHeader_2.54mm:PinHeader_1x05_P2.54mm_Vertical')
define('Reset_Button',[('1','NRST','passive'),('2','GND','passive')],shape='R')
part(mcu,'SW1300','Reset_Button',{'1':'MCU_NRST','2':'GND'},mpn='RESET_SWITCH_SELECTION_REQUIRED')
passive(mcu,'R1300','10k','V3V3','MCU_NRST')
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
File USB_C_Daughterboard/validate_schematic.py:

"""Check generated syntax, KiCad connectivity, and critical daughterboard invariants."""

from pathlib import Path
import csv
import json
import subprocess
import tempfile
import xml.etree.ElementTree as ET
import sexpdata

ROOT = Path(__file__).resolve().parent
PROJECT_ROOT = ROOT.parent
CLI = Path(r"C:\Program Files\KiCad\9.0\bin\kicad-cli.exe")


def validate():
    root = sexpdata.loads((PROJECT_ROOT/'XG_Mobile_USB_Hub.kicad_sch').read_text(encoding='utf-8'))
    children = [item for item in root if isinstance(item,list) and str(item[0]) == 'sheet']
    child_files = [str(field[2]) for child in children for field in child
                   if isinstance(field,list) and str(field[0]) == 'property' and field[1] == 'Sheetfile']
    assert sorted(child_files) == ['XG_Mobile_USB_Hub_MCU.kicad_sch','XG_Mobile_USB_Hub_Power.kicad_sch','XG_Mobile_USB_Hub_USB_Hub.kicad_sch']
    assert {path.name for path in PROJECT_ROOT.glob('XG_Mobile_USB_Hub*.kicad_sch')} == set(child_files+['XG_Mobile_USB_Hub.kicad_sch'])
    assert not list(ROOT.glob('*.kicad_sch')), 'Obsolete nested schematics remain'
    direct_wires = 0
    local_labels = []
    global_labels = []
    power_symbols = []
    for path in PROJECT_ROOT.glob('XG_Mobile_USB_Hub*.kicad_sch'):
        parsed = sexpdata.loads(path.read_text(encoding='utf-8'))
        assert str(parsed[0]) == 'kicad_sch', path
        for item in parsed:
            if isinstance(item,list) and str(item[0]) in ['label','global_label']:
                (local_labels if str(item[0])=='label' else global_labels).append(str(item[1]))
                effect = next(field for field in item if isinstance(field,list) and str(field[0])=='effects')
                font = next(field for field in effect if isinstance(field,list) and str(field[0])=='font')
                size = next(field for field in font if isinstance(field,list) and str(field[0])=='size')
                assert size[1:] == [1.27,1.27]
            if isinstance(item,list) and str(item[0])=='symbol':
                fields = {str(field[0]):field for field in item if isinstance(field,list)}
                properties = {str(field[1]):str(field[2]) for field in item
                              if isinstance(field,list) and str(field[0])=='property'}
                if properties.get('Reference','').startswith('#PWR'):
                    power_symbols.append(item)
                    assert str(fields['in_bom'][1]) == str(fields['on_board'][1]) == 'no'
            if isinstance(item,list) and str(item[0])=='wire':
                points = next(field for field in item if isinstance(field,list) and str(field[0])=='pts')[1:]
                length = abs(float(points[0][1])-float(points[1][1]))+abs(float(points[0][2])-float(points[1][2]))
                direct_wires += length>5.09
    assert direct_wires>=100, 'Expected directly wired functional groups, not only label stubs'
    assert len(local_labels)>100 and len(power_symbols)>100
    assert not {'GND','VIN12','V5','V3V3','VCORE'} & set(local_labels+global_labels)
    expected = [component for component in json.loads((ROOT/'connectivity.json').read_text()) if component['physical']]
    assert {component['sheet'] for component in expected} == {'Power','MCU','USB_Hub'}
    net_sheets = {}
    for component in expected:
        for net in component['nets'].values():
            if net:
                net_sheets.setdefault(net,set()).add(component['sheet'])
    assert all(len(net_sheets[net])==1 for net in local_labels)
    assert all(len(net_sheets[net])>1 for net in global_labels)
    with tempfile.TemporaryDirectory() as directory:
        netlist_path = Path(directory)/'netlist.xml'
        subprocess.run([str(CLI), 'sch', 'export', 'netlist', '--format', 'kicadxml', '--output', str(netlist_path), str(PROJECT_ROOT/'XG_Mobile_USB_Hub.kicad_sch')], check=True)
        netlist = ET.parse(netlist_path)
    actual_full = {(node.get('ref'), node.get('pin')): net.get('name')
              for net in netlist.findall('.//nets/net') for node in net.findall('node')}
    actual = {pin:net.rsplit('/',1)[-1] for pin,net in actual_full.items()}
    expected_groups,actual_groups = {},{}
    for component in expected:
        for pin,net in component['nets'].items():
            if net is not None:
                node = (component['ref'],pin)
                expected_groups.setdefault(net,set()).add(node)
                actual_groups.setdefault(actual_full.get(node),set()).add(node)
    assert {frozenset(nodes) for nodes in expected_groups.values()} == {frozenset(nodes) for nodes in actual_groups.values()}, 'Net split or short after label conversion'
    errors = [(component['ref'], pin, net, actual.get((component['ref'], pin)))
              for component in expected for pin, net in component['nets'].items()
              if net is not None and actual.get((component['ref'], pin)) != net]
    assert not errors, errors
    assert len(netlist.findall('.//components/comp')) == len(expected)
    components = {component['ref']: component for component in expected}
    sourced_ics = {
        'U101': ('LM51772RHAR','C41383743'),
        'U201': ('TPS40305DRCR','C140285'),
        'U301': ('TPS56A37RPAR','C22392669'),
        'U401': ('TPS62130RGTR','C43590'),
        'U501': ('USB7206CT/KDX','C3210691'),
        'U600': ('HD3SS3220IRNHR','C701817'),
        'U700': ('HD3SS3220IRNHR','C701817'),
        'U1200': ('TCPP03-M20','C3662955'),
        'U1201': ('HD3SS3212IRKSR','C544517'),
        'U1300': ('STM32G071CBT6','C432212'),
    }
    for ref, identifiers in sourced_ics.items():
        assert (components[ref]['mpn'],components[ref]['lcsc']) == identifiers, ref
    with (ROOT/'BOM.csv').open(newline='',encoding='utf-8') as stream:
        bom = csv.DictReader(stream)
        assert 'Part_Number' in bom.fieldnames and 'MPN' not in bom.fieldnames
        bom_rows = list(bom)
    assert len(bom_rows) == len(expected)
    for component in netlist.findall('.//components/comp'):
        fields = {field.get('name'):field.text or '' for field in component.findall('./fields/field')}
        assert 'MPN' not in fields
        assert fields['Part_Number'] == components[component.get('ref')]['mpn']
        assert fields.get('LCSC','') == components[component.get('ref')]['lcsc']
    for ref in ['J600','J700','J1200']:
        nets = components[ref]['nets']
        assert nets['A6'] == nets['B6']
        assert nets['A7'] == nets['B7']
        assert len({nets[pin] for pin in ['A4','A9','B4','B9']}) == 1
    assert components['U501']['nets']['9'] == 'VCORE'
    assert components['U501']['nets']['2'] == 'HUB_VBUS_DET'
    assert components['U101']['nets']['5'] == components['U1300']['nets']['46'] == 'I2C_SDA'
    assert components['U101']['nets']['6'] == components['U1300']['nets']['45'] == 'I2C_SCL'
    assert components['U101']['nets']['9'] == 'GND'
    assert components['U101']['nets']['14'] == 'PD_VCC2'
    assert components['U1300']['nets']['28'] == components['U1200']['nets']['1'] == 'MCU_CC1'
    assert components['U1300']['nets']['27'] == components['U1200']['nets']['3'] == 'MCU_CC2'
    assert components['U1300']['footprint'] == 'Package_QFP:LQFP-48_7x7mm_P0.5mm'
    assert set(components['U1300']['nets']) == {str(pin) for pin in range(1,49)}
    for pin in ['4','5','6']:
        assert components['U1300']['nets'][pin] == 'V3V3'
    for pin in ['7','29','32']:
        assert components['U1300']['nets'][pin] == 'GND'
    for pin,net in {'10':'MCU_NRST','35':'SWDIO','36':'SWCLK','38':'UP_FAULT_N',
                    '39':'PD_NFLT','40':'UP_MUX_SEL','41':'UP_MUX_OEN','48':'3V3_PG'}.items():
        assert components['U1300']['nets'][pin] == net
    for ref in ['C1304','C1305','C1306']:
        assert components[ref]['nets'] == {'1':'V3V3','2':'GND'}
    assert components['U600']['nets']['30'] == components['U700']['nets']['30'] == 'V5'
    assert components['J1100']['kind'] == 'USB_A'
    for base,port in [(800,3),(900,4),(1000,5),(1100,6)]:
        bulk = components[f'C{base+4}']
        assert bulk['value'] == '220uF 10V +/-20% low ESR'
        assert bulk['nets'] == {'1':f'P{port}_VBUS','2':'GND'}
    assert components['L101']['mpn'] == 'APS1040M2R2A'
    assert abs(0.6*(1+45.3/10)-3.3) < 0.03
    assert abs(0.6*(1+10/1.37)-5) < 0.03
    assert 1.09 < 0.8*(1+43.7/100) < 1.21
    print(f"PASS: {len(expected)} components and {sum(net is not None for component in expected for net in component['nets'].values())} connected pins match KiCad export")


if __name__ == '__main__':
    validate()
